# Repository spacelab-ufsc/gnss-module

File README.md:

<h1 align="center">
	GNSS POD Holder - Global Navigation Satellite System & Precise Orbit Determination Holder
	<br>
</h1>

<h4 align="center">PCB Holder for the OEM719 Novatel by Spacelab.</h4>

<p align="center">
  	<a href="#overview">Overview</a> •
  	<a href="#repository-organization">Repository Organizarion</a> •
  	<a href="#license">License</a> •
  	<a href="#releases">Releases</a> •
  	<a href="#notes">Notes</a>
</p>

## Overview

WIP...

## Repository Organization
	- doc: Technical GNSS Pod Holder documentation (including firmware, hardware, user guide, and datasheet).
	- firmware: GNSS Pod Holder firmware project (sources and configs).
	- hardware: GNSS Pod Holder hardware project (sources and outputs).

## License

This project is open-source and under the GPLv3 license, but some third-part files and libraries are subjected to specific terms and comercial use might be prohibited. Therefore, the purpose of the open access approach is to support further educational use and academic projects.

## Releases

WIP...
<!-- The GNSS POD software and hardware releases are synchronized in order to garantee compatibility. Then, using diferent versions might lead to unpredictable behavior. Refer to the [documentation]() for compatibility notes. -->

## Notes

<!-- More info about the GNSS POD target mission: [FloripaSat-RO]()) -->

More info about the SpaceLab: [GitHub](https://github.com/spacelab-ufsc/spacelab) and [Website](https://spacelab.ufsc.br/en/home/)

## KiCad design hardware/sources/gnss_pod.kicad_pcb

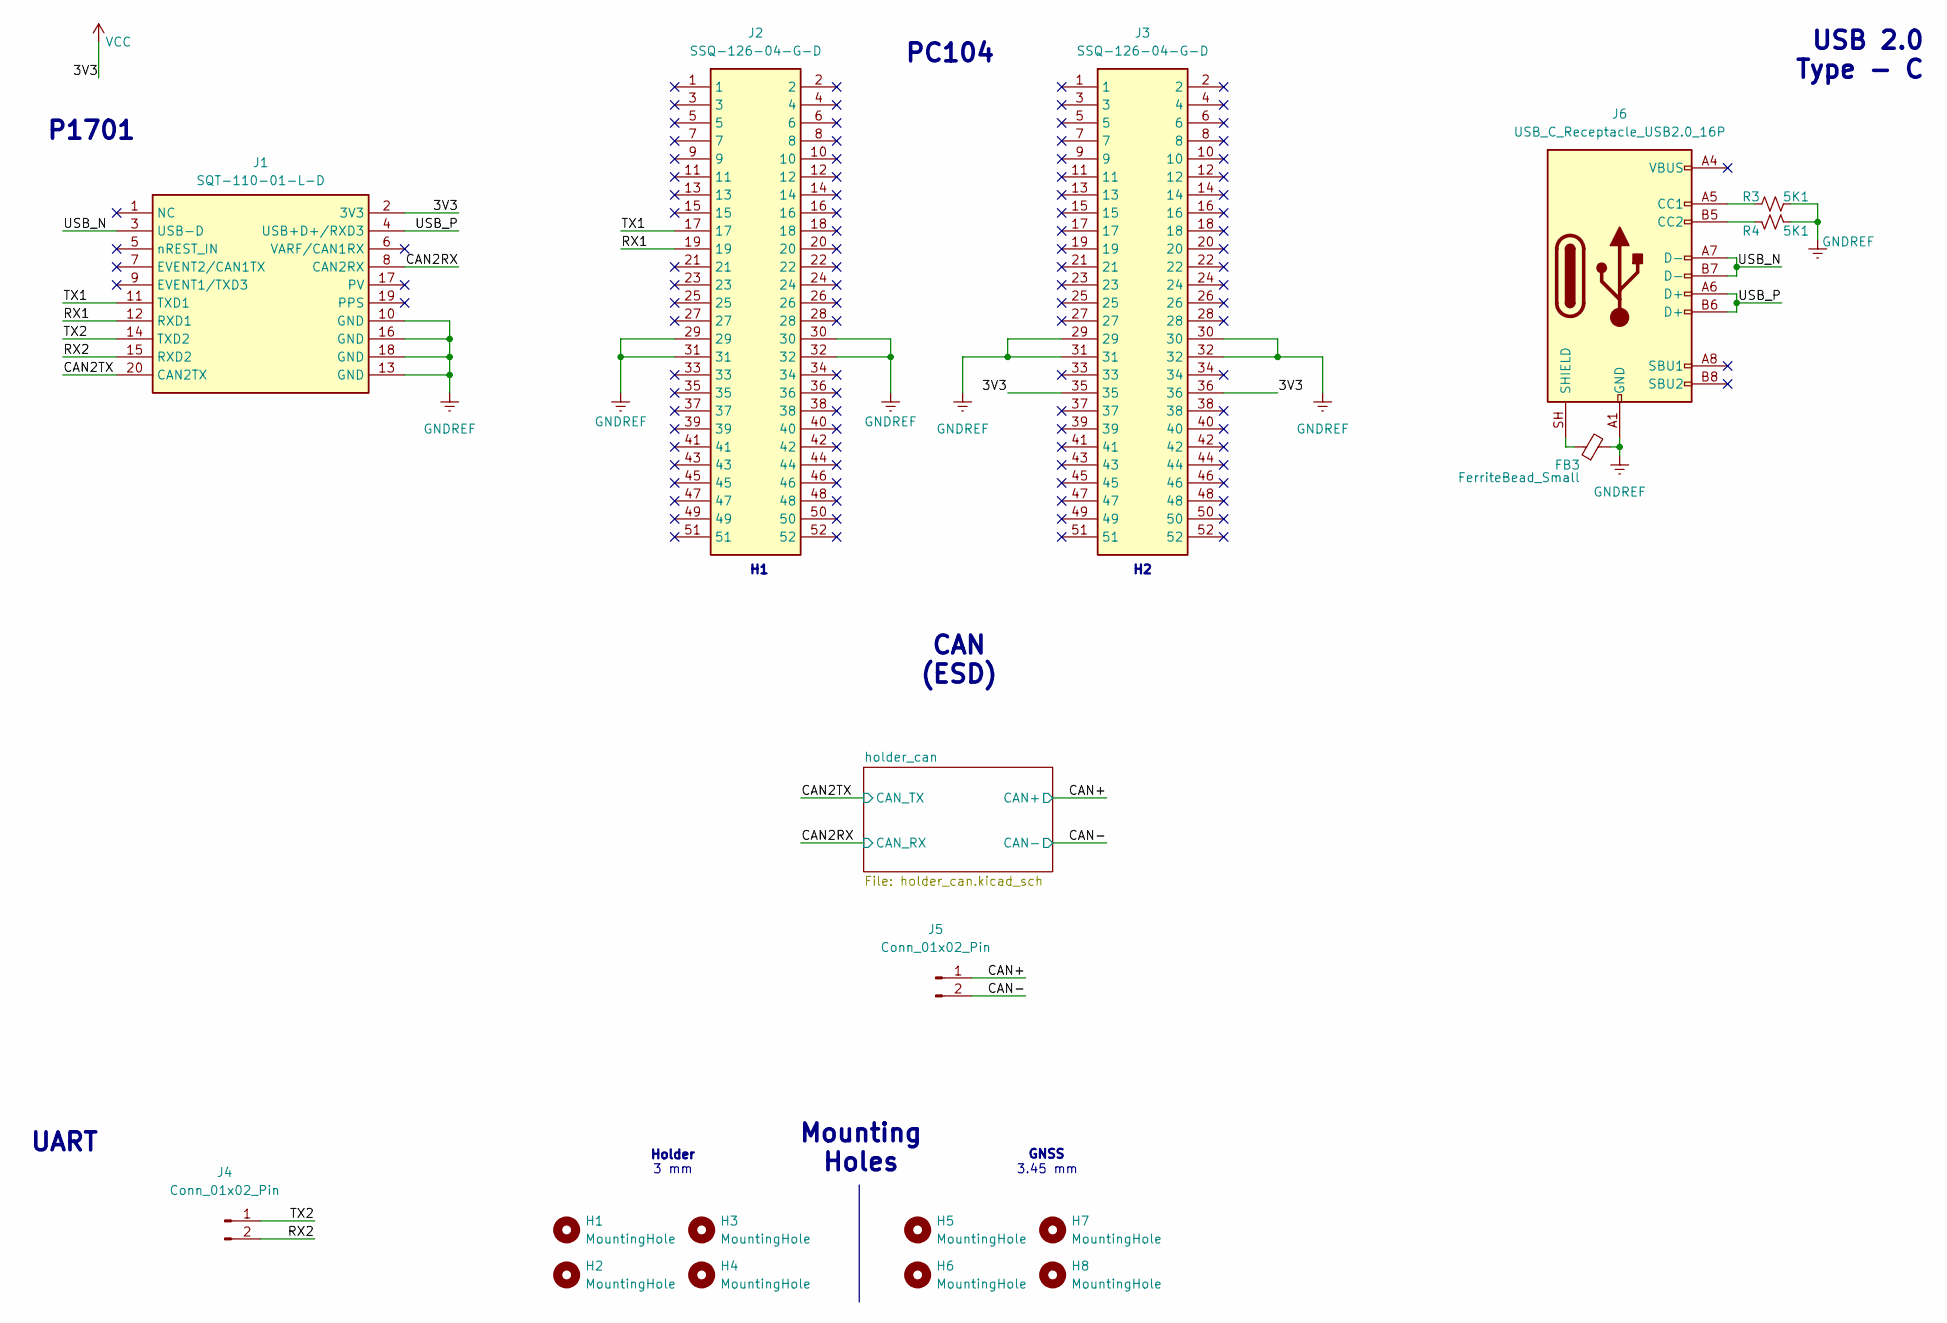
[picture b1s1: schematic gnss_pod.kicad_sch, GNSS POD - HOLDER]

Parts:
FB3: FerriteBead_Small; L_0603_1608Metric
H1, H2, H3, H4, H5, H6, H7, H8: MountingHole; MountingHole_3mm_Pad
J1: SQT-110-01-L-D; SQT11001LD; Mouser Part Number 200-SQT11001LD
J2, J3: SSQ-126-04-G-D; RHDR52W64P254_2X26_6655X495X864P; Mouser Part Number 200-SSQ12604GD
J4, J5: Conn_01x02_Pin; 532614002
J6: USB_C_Receptacle_USB2.0_16P; USB4110GFA
R3, R4: 5K1; R_0603_1608Metric

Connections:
/CAN2RX: J1.8 (CAN2RX); also elsewhere on the board
/CAN2TX: J1.20 (CAN2TX); also elsewhere on the board
/CAN+: J5.1; also elsewhere on the board
/CAN-: J5.2; also elsewhere on the board
/RX1: J1.12 (RXD1), J2.19
/RX2: J1.15 (RXD2), J4.2
/TX1: J1.11 (TXD1), J2.17
/TX2: J1.14 (TXD2), J4.1
/USB_N: J1.3 (USB-D), J6.A7 (D-), J6.B7 (D-)
/USB_P: J1.4 (USB+D+/RXD3), J6.A6 (D+), J6.B6 (D+)
GNDREF: FB3.2, J1.10 (GND), J1.13 (GND), J1.16 (GND), J1.18 (GND), J2.29, J2.30, J2.31, J2.32, J3.29, J3.30, J3.31, J3.32, J6.A1 (GND), J6.A12 (GND), J6.B1 (GND), J6.B12 (GND), R3.2, R4.2; also elsewhere on the board
unnamed: J6.A5 (CC1), R3.1
unnamed: J6.B5 (CC2), R4.1
unnamed: FB3.1, J6.SH (SHIELD)
VCC: J1.2 (3V3), J3.35, J3.36; also elsewhere on the board

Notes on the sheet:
UART
PC104
3 mm
CAN (ESD)
P1701
USB 2.0 Type - C
Holder
3.45 mm
GNSS
Mounting Holes

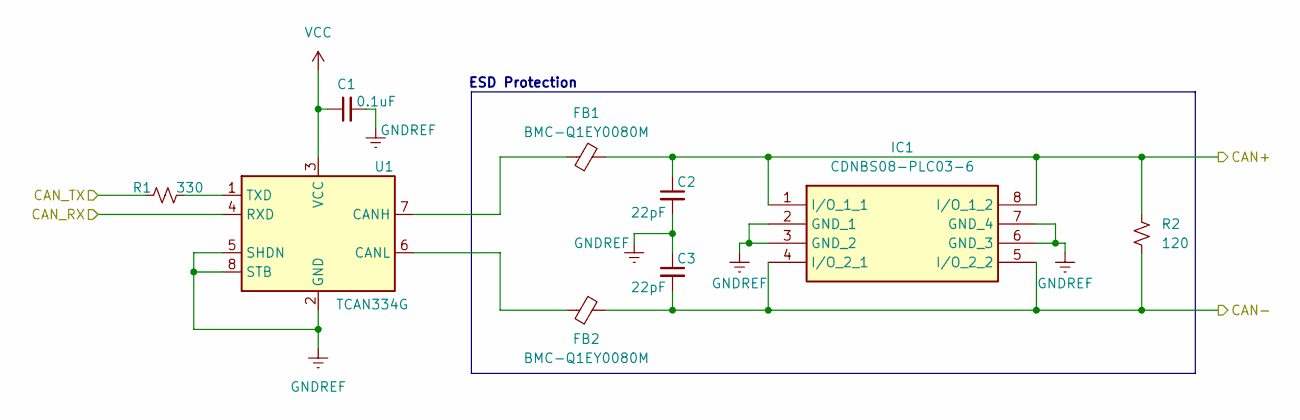
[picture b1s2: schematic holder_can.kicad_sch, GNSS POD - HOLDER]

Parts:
C1: 0.1uF; C_0603_1608Metric_Pad1.08x0.95mm_HandSolder
C2, C3: 22pF; C_0603_1608Metric_Pad1.08x0.95mm_HandSolder
FB1, FB2: BMC-Q1EY0080M; L_0402_1005Metric_Pad0.77x0.64mm_HandSolder
IC1: CDNBS08-PLC03-6; SOIC127P600X175-8N; Mouser Part Number 652-CDNBS08-PLC03-6
R1: 330; R_0603_1608Metric_Pad0.98x0.95mm_HandSolder
R2: 120; R_0603_1608Metric_Pad0.98x0.95mm_HandSolder
U1: TCAN334G; SOIC127P600X175-8N

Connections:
/CAN2RX: U1.4 (RXD); also elsewhere on the board
/CAN2TX: R1.1; also elsewhere on the board
/CAN+: C2.1, FB1.2, IC1.1 (I/O_1_1), IC1.8 (I/O_1_2), R2.1; also elsewhere on the board
/CAN-: C3.2, FB2.2, IC1.4 (I/O_2_1), IC1.5 (I/O_2_2), R2.2; also elsewhere on the board
GNDREF: C1.2, C2.2, C3.1, IC1.2 (GND_1), IC1.3 (GND_2), IC1.6 (GND_3), IC1.7 (GND_4), U1.2 (GND), U1.5 (SHDN), U1.8 (STB); also elsewhere on the board
unnamed: FB1.1, U1.7 (CANH)
unnamed: FB2.1, U1.6 (CANL)
unnamed: R1.2, U1.1 (TXD)
VCC: C1.1, U1.3 (VCC); also elsewhere on the board

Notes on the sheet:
ESD Protection

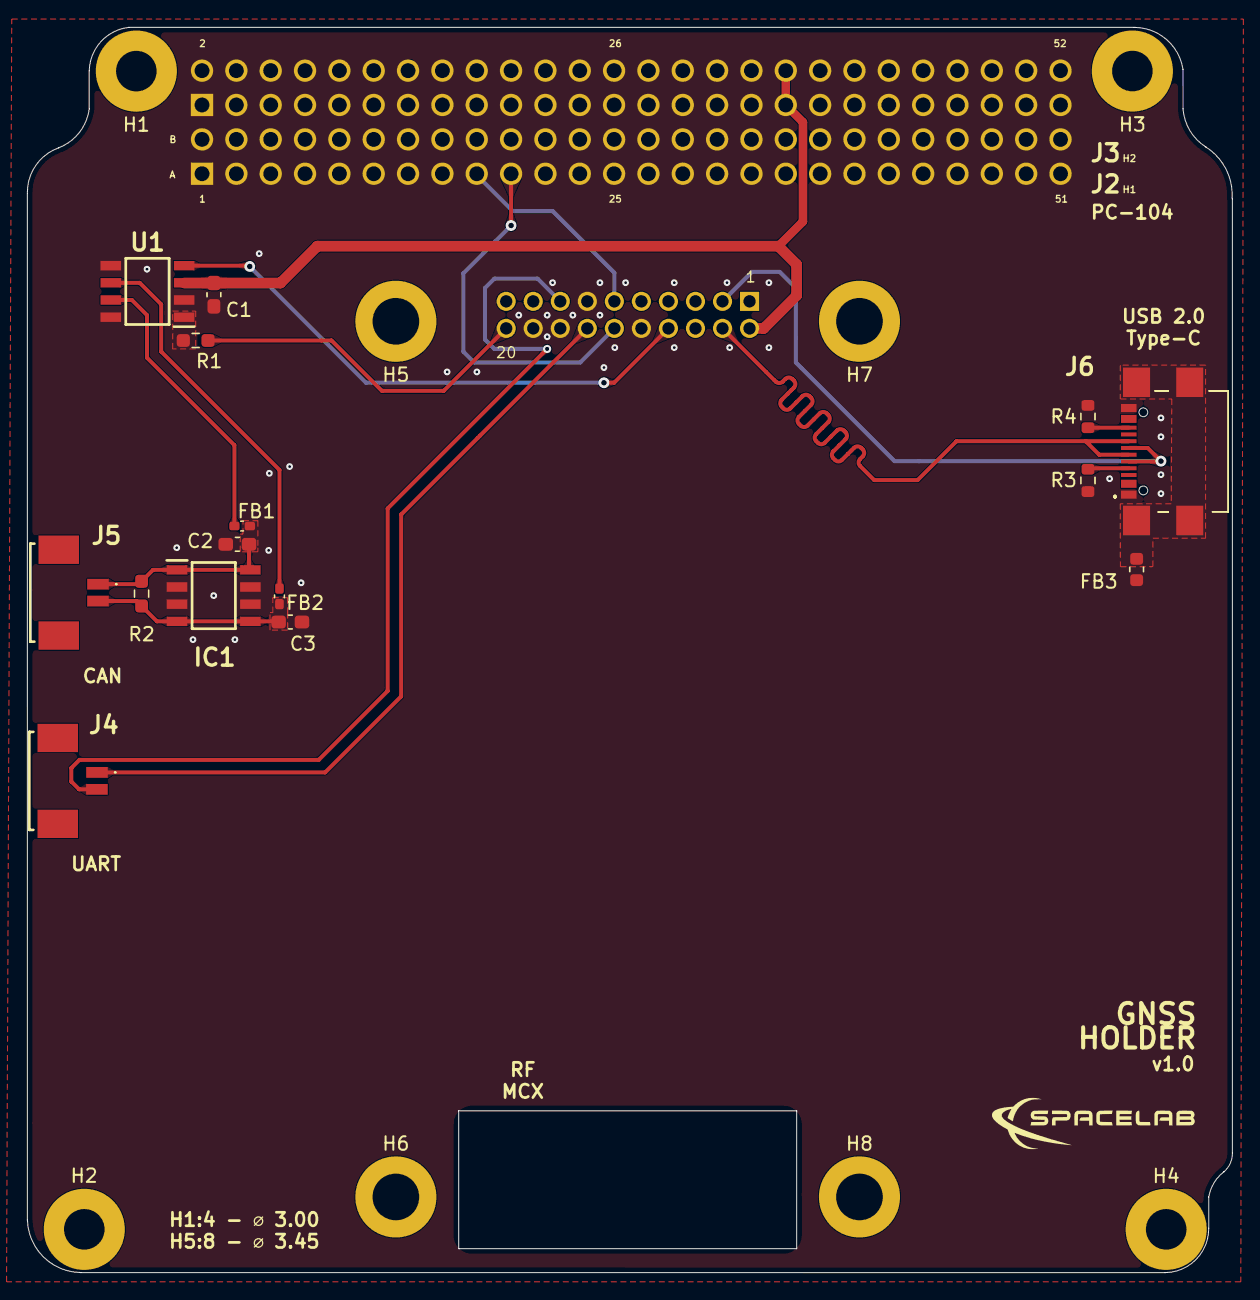
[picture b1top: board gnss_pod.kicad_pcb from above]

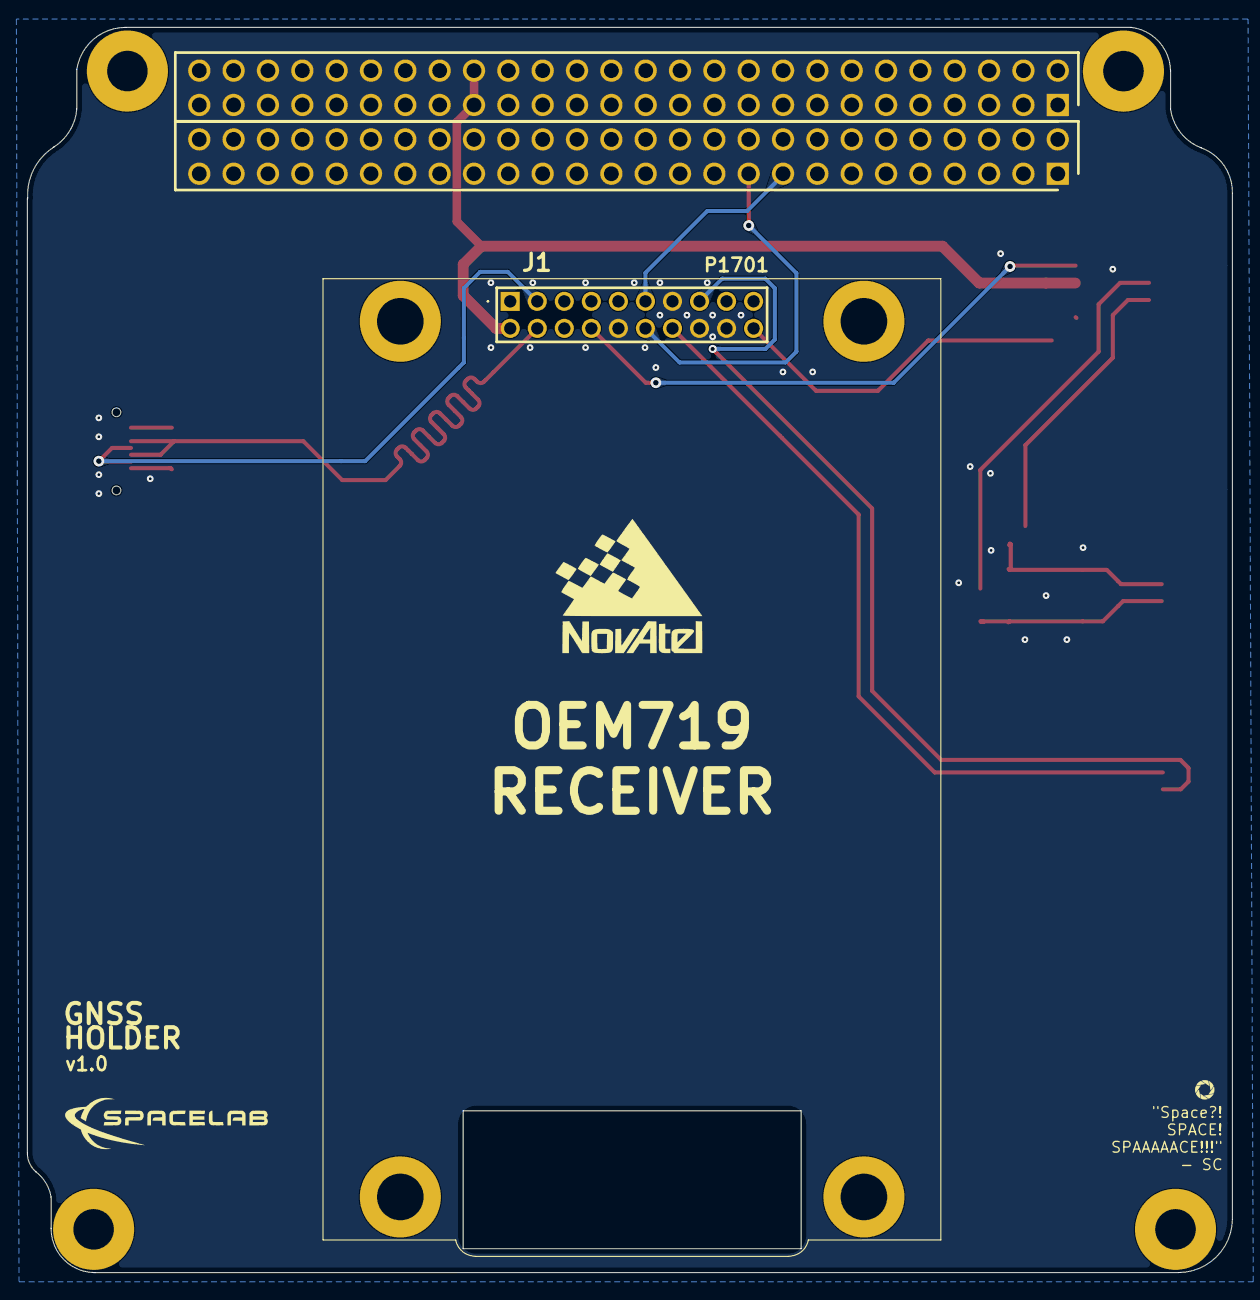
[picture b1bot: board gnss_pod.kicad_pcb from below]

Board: 2 copper layers, 89.1 x 92.1 mm, 26 parts (3 on the bottom side), 18 nets.

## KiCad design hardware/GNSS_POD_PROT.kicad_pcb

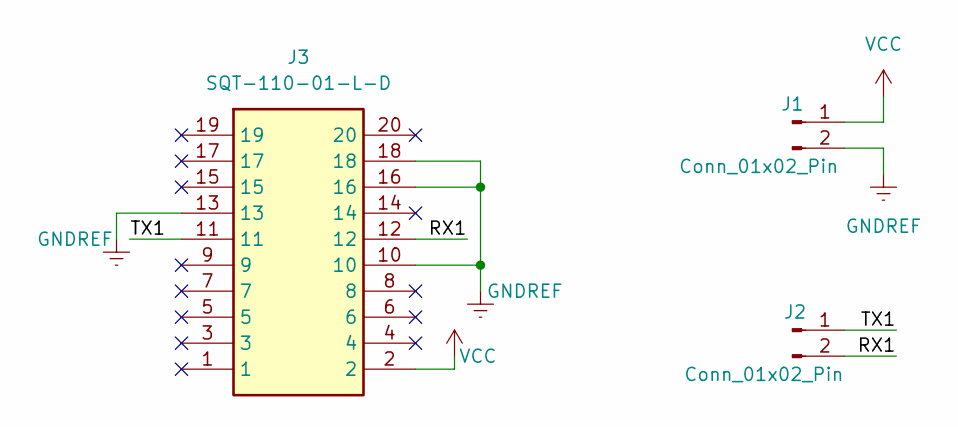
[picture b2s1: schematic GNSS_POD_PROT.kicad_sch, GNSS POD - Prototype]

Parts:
J1, J2: Conn_01x02_Pin; PinHeader_1x02_P2.54mm_Vertical
J3: SQT-110-01-L-D; SQT11001LD; Mouser Part Number 200-SQT11001LD

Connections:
/RX1: J2.2, J3.12
/TX1: J2.1, J3.11
GNDREF: J1.2, J3.10, J3.13, J3.16, J3.18
VCC: J1.1, J3.2

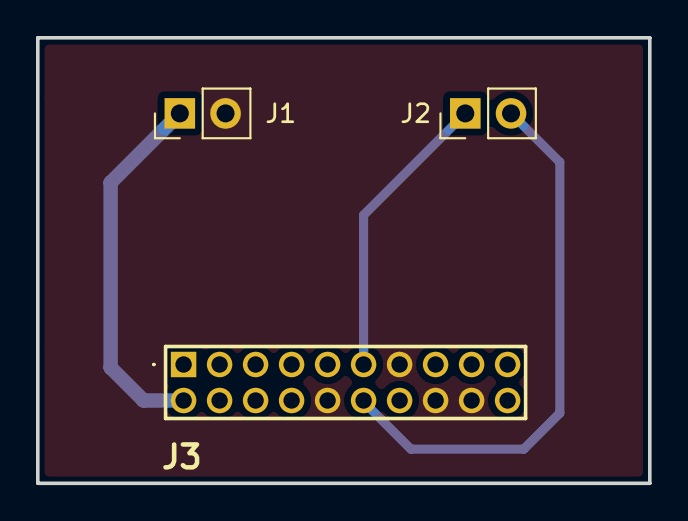
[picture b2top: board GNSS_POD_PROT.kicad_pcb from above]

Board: 2 copper layers, 34.0 x 24.8 mm, 3 parts (0 on the bottom side), 4 nets.

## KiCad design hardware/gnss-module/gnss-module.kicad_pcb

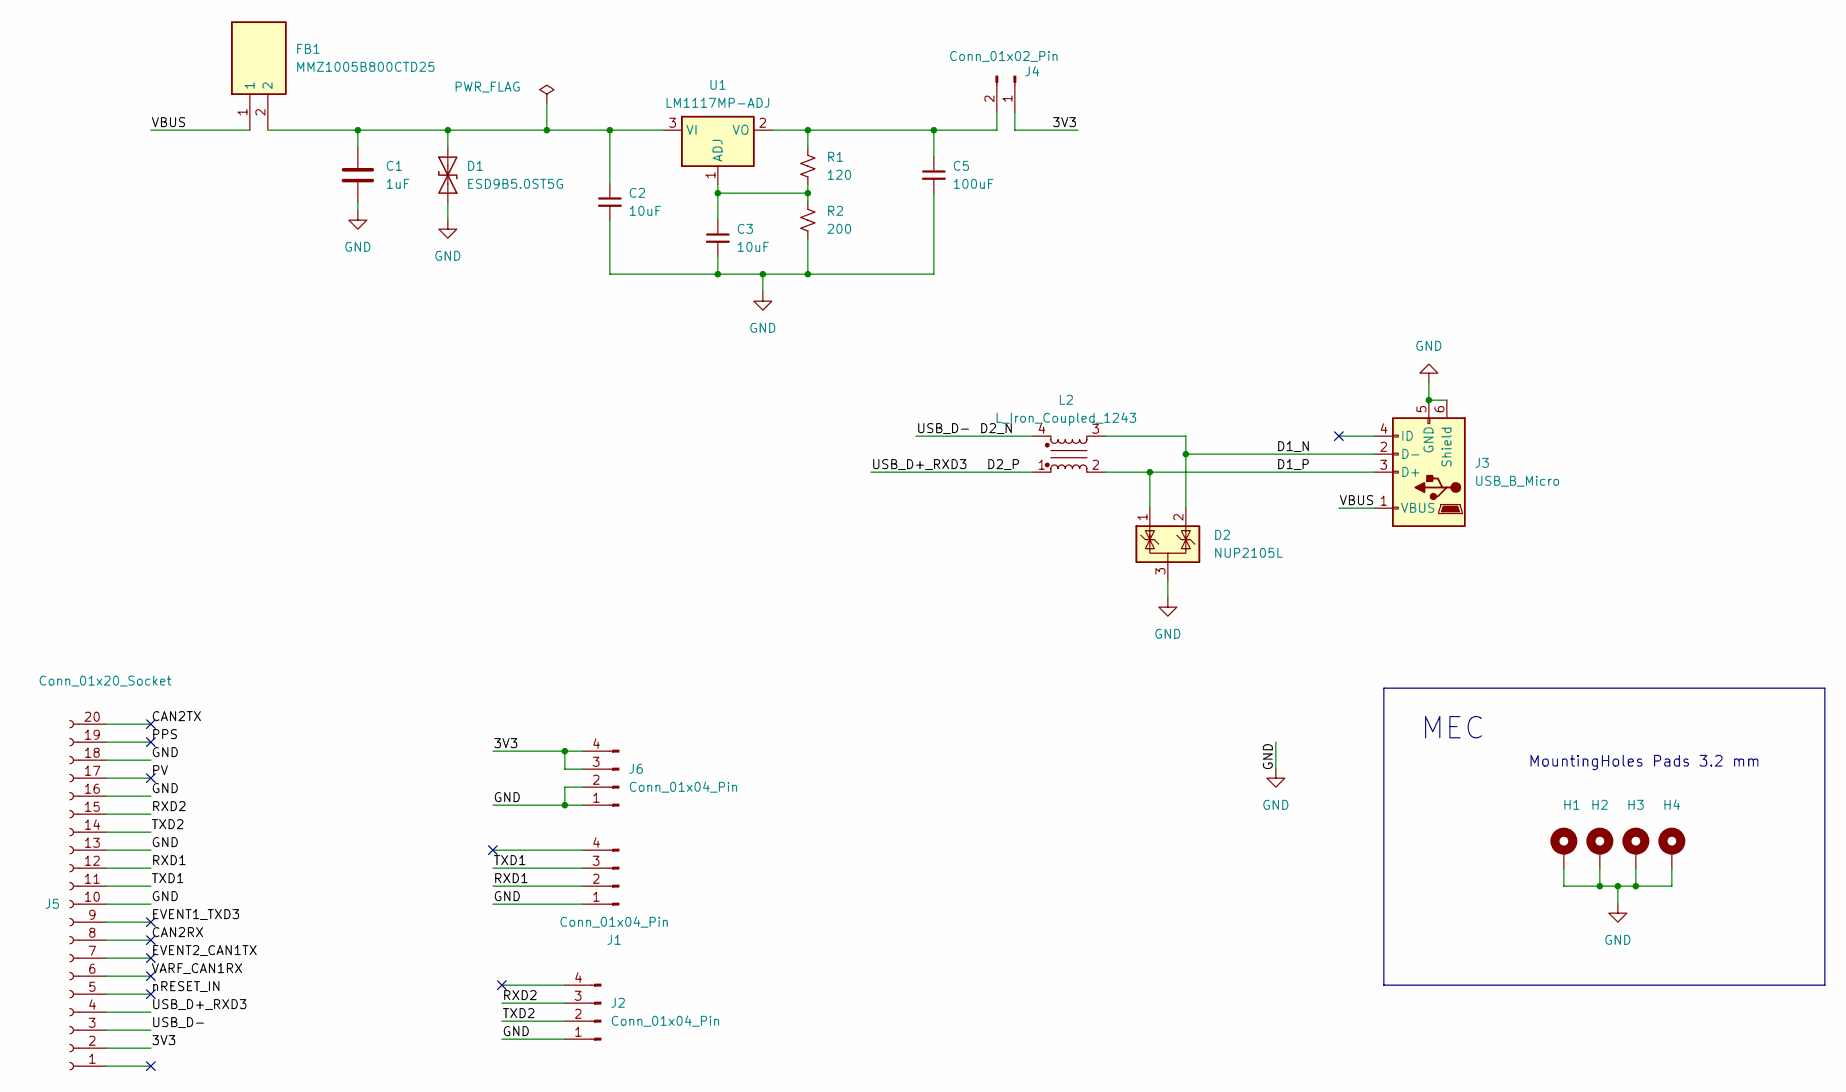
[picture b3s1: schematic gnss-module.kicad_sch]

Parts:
C1: 1uF; C_0603_1608Metric_Pad1.08x0.95mm_HandSolder
C2, C3: 10uF; C_0603_1608Metric_Pad1.08x0.95mm_HandSolder
C5: 100uF; C_0603_1608Metric_Pad1.08x0.95mm_HandSolder
D1: ESD9B5.0ST5G; SOD-523_0P9X1P3_ONS-M
D2: NUP2105L; SOT-723_0P85X1P25_ONS-M
FB1: MMZ1005B800CTD25; BEADC1005X55N; Mouser Part Number 810-MMZ1005B800CTD25
H1, H2, H3, H4: MountingHole_Pad; MountingHole_3.2mm_M3_DIN965_Pad
J1, J2, J6: Conn_01x04_Pin; Molex_PicoBlade_53398-0471_1x04-1MP_P1.25mm_Vertical
J3: USB_B_Micro; CONN_10104110-0001LF_AMP
J4: Conn_01x02_Pin; PinHeader_1x02_P1.27mm_Vertical
J5: Conn_01x20_Socket; SAMTEC-SQW-110-01-X-D-VS
L2: L_Iron_Coupled_1243; 744230900
R1: 120; R_0603_1608Metric_Pad0.98x0.95mm_HandSolder
R2: 200; R_0603_1608Metric_Pad0.98x0.95mm_HandSolder
U1: LM1117MP-ADJ; SOT-223-3_TabPin2

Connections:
/3V3: J4.1, J5.2, J6.3, J6.4
/CAN2RX: J5.8
/CAN2TX: J5.20
/D1_N: D2.2 (K), J3.2 (D-), L2.3
/D1_P: D2.1 (K), J3.3 (D+), L2.2
/D2_N: J5.3, L2.4
/D2_P: J5.4, L2.1
/EVENT1_TXD3: J5.9
/EVENT2_CAN1TX: J5.7
/PPS: J5.19
/PV: J5.17
/RXD1: J1.2, J5.12
/RXD2: J2.3, J5.15
/TXD1: J1.3, J5.11
/TXD2: J2.2, J5.14
/VARF_CAN1RX: J5.6
/VBUS: FB1.1, J3.1 (VBUS)
/nRESET_IN: J5.5
GND: C1.2, C2.2, C3.2, C5.2, D1.1 (A1), D2.3 (A), H1.1, H2.1, H3.1, H4.1, J1.1, J2.1, J3.5 (GND), J3.6 (Shield), J5.10, J5.13, J5.16, J5.18, J6.1, J6.2, R2.2
unnamed: C1.1, C2.1, D1.2 (A2), FB1.2, U1.3 (VI)
unnamed: C5.1, J4.2, R1.1, U1.2 (VO)
unnamed: C3.1, R1.2, R2.1, U1.1 (ADJ)

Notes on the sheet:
MEC
MountingHoles Pads 3.2 mm

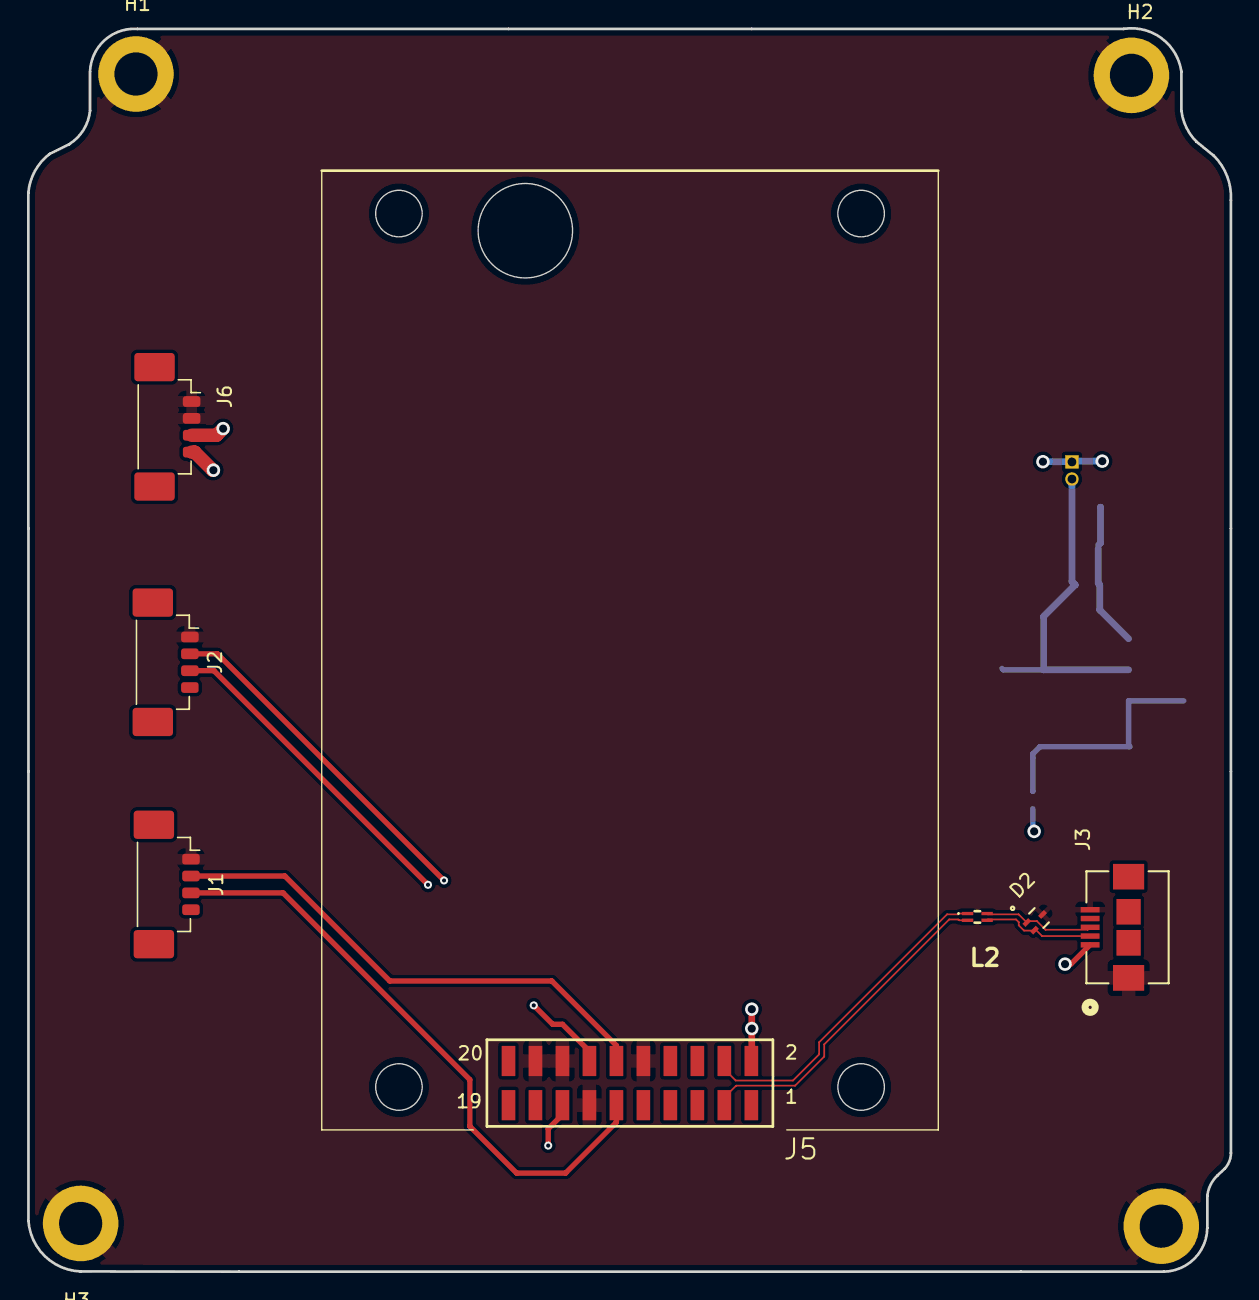
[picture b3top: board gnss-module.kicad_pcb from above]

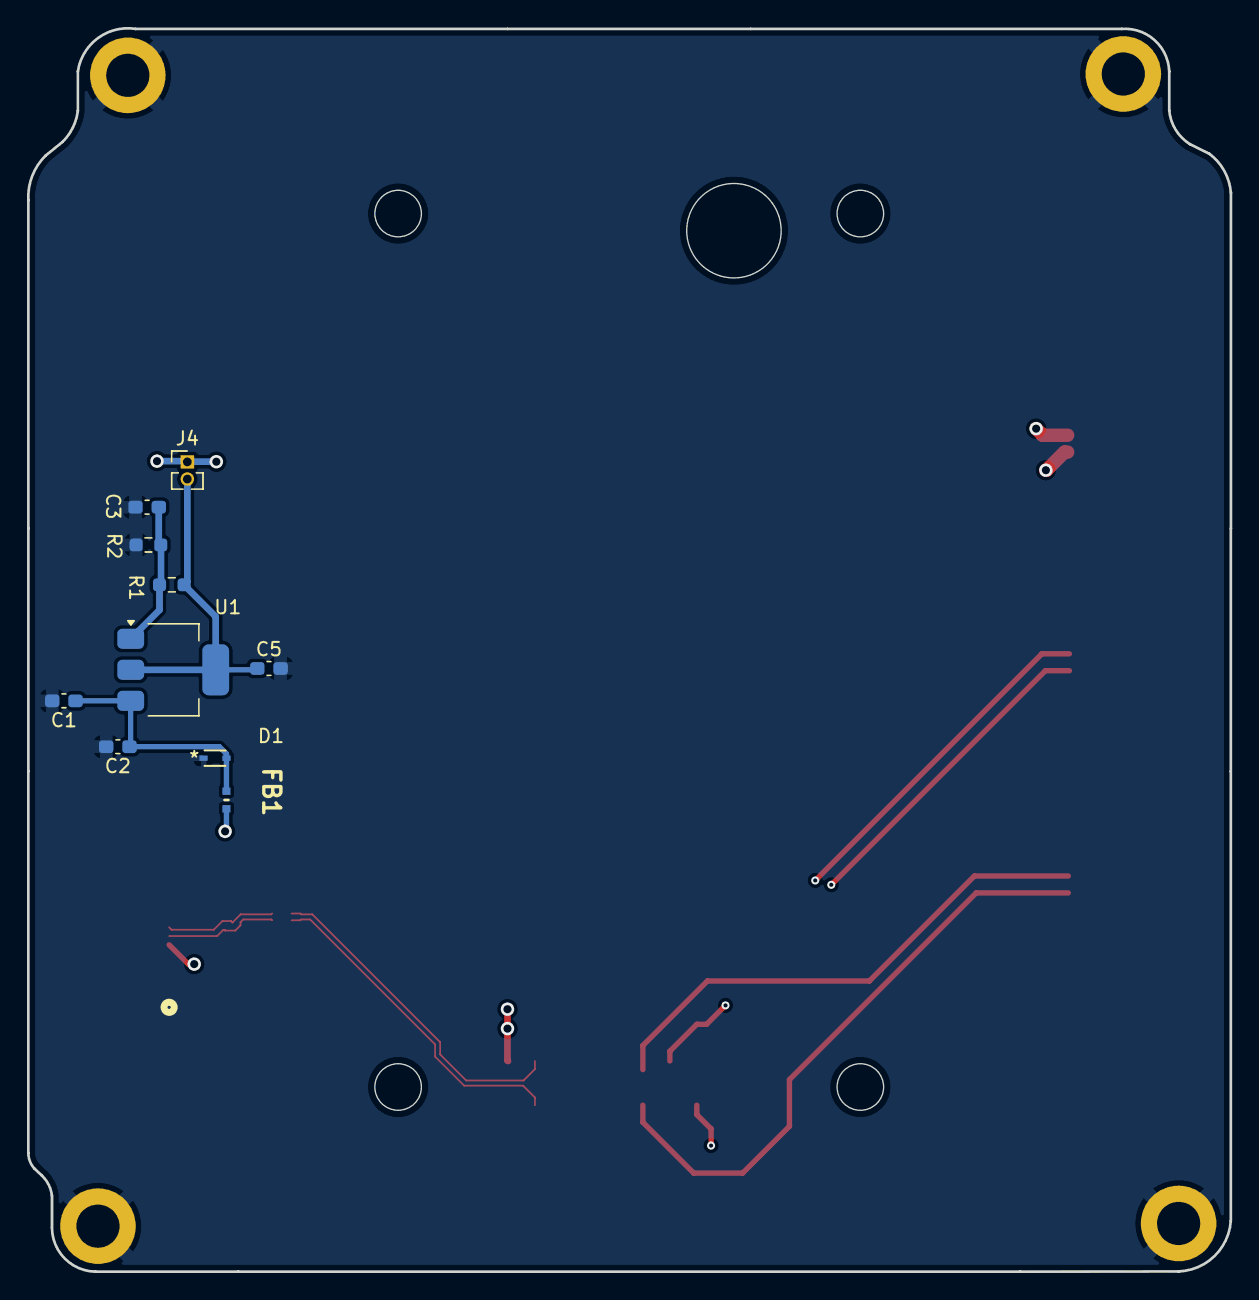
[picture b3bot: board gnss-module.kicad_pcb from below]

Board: 4 copper layers, 89.1 x 92.2 mm, 21 parts (10 on the bottom side), 14 nets.

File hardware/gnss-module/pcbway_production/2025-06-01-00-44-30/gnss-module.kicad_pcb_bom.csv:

Designator,Quantity,Value,Footprint,Package,MPN,DNP,Mount_Type,Description,Height,Mouser Part Number,Mouser Price/Stock,Manufacturer_Name
C1,1,1uF,C_0603_1608Metric_Pad1.08x0.95mm_HandSolder,,,,smt,Unpolarized capacitor,,,,
"C2, C3",2,10uF,C_0603_1608Metric_Pad1.08x0.95mm_HandSolder,,,,smt,"Unpolarized capacitor, small symbol",,,,
C5,1,100uF,C_0603_1608Metric_Pad1.08x0.95mm_HandSolder,,,,smt,"Unpolarized capacitor, small symbol",,,,
D1,1,ESD9B5.0ST5G,SOD-523_0P9X1P3_ONS-M,,,,smt,"ESD protection diode, 5.0Vrwm, SOD-923",,,,
D2,1,NUP2105L,SOT-723_0P85X1P25_ONS-M,,,,smt,"Dual Line CAN Bus Protector, 24Vrwm",,,,
FB1,1,MMZ1005B800CTD25,BEADC1005X55N,,MMZ1005B800CTD25,,smt,Ferrite Beads Multi-Layer 80Ohm 25% 100MHz 450mA 190mOhm DCR 0402 Automotive T/R,0.55,810-MMZ1005B800CTD25,https://www.mouser.co.uk/ProductDetail/TDK/MMZ1005B800CTD25?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,TDK
"H1, H2, H3, H4",4,MountingHole_Pad,MountingHole_3.2mm_M3_DIN965_Pad,,,,tht,Mounting Hole with connection,,,,
"J1, J2, J6",3,Conn_01x04_Pin,Molex_PicoBlade_53398-0471_1x04-1MP_P1.25mm_Vertical,,,,smt,"Generic connector, single row, 01x04, script generated",,,,
J3,1,USB_B_Micro,CONN_10104110-0001LF_AMP,,,,smt,USB Micro Type B connector,,,,
J4,1,Conn_01x02_Pin,PinHeader_1x02_P1.27mm_Vertical,,,,tht,"Generic connector, single row, 01x02, script generated",,,,
J5,1,Conn_01x20_Socket,PinSocket_2x10_P2.00mm_Vertical_SMD,,,,smt,"Generic connector, single row, 01x20, script generated",,,,
L2,1,L_Iron_Coupled_1243,744230900,,,,smt,Coupled inductor with iron core,,,,
R1,1,120,R_0603_1608Metric_Pad0.98x0.95mm_HandSolder,,,,smt,"Resistor, small US symbol",,,,
R2,1,200,R_0603_1608Metric_Pad0.98x0.95mm_HandSolder,,,,smt,"Resistor, small US symbol",,,,
U1,1,LM1117MP-ADJ,SOT-223-3_TabPin2,,,,smt,"800mA Low-Dropout Linear Regulator, adjustable output, SOT-223",,,,

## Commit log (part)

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2025-06-01 main: hardware folder with project added
2025-06-01 main: Socket connector changed
2025-07-29 main: README.md: Overview added
2026-05-17 update folder
2026-05-17 needs review
2026-05-18 Updated layout + schematic
2026-05-25 Some changes, wip usb, layout wip
2026-06-18 Layout modified according to INEP requirements
